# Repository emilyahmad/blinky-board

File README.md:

# Blinky board

This toro inoue inspired 555 LED chaser board contains 2 IC's: CD4017 to control LED's flashing and get input from NE555P, 2 header pins to power the circuit, standard capacitors and resistors, and of course LEDs. LEDs blink using the 555's astable mode to produces a continuous oscillating signal by toggling its output between high and low Made with help from @Tanishq Goyal qnd @CAN's guides on stasis.

# Photos

| Schematic                          | PCB                    | 3D Viewer            |
| ---------------------------------- | ---------------------- | -------------------- |
|  |  |  |

# Physical PCB / After Soldering

| Front                              | Back                             | Powered                                 |
| ---------------------------------- | -------------------------------- | --------------------------------------- |
|  |  |  |

# BOM

(Technically just using the blinky board kit from Hack Club)

| Item                                    | Purpose                          | Quantity |
| --------------------------------------- | -------------------------------- | -------- |
| C1                                      | 1F capacitor                     | 1        |
| C2                                      | .1F capacitor                    | 1        |
| D1, D2, D3, D4, D5, D6, D7, D8, D9, D10 | LEDs various colors              | 10       |
| J1                                      | 01x02 pin socket                 | 1        |
| J2                                      | 01x01 pin socket                 | 1        |
| R1                                      | 1k resistor                      | 1        |
| RV1                                     | 470 ohm resistor                 | 1        |
| U1                                      | NE555P IC (with timer we'll use) | 1        |
| U2                                      | 4017 IC (extend GPIO of NE555P)  | 1        |

Total: $10.60

```
⠀⠀⠀⠀⠀⠀⠀⠀⠀⠀⠀⠀⠀⠀⠀⠀⠀⠀⠀⠀⠀⠀⠀⠀⠀⠀⠀⠀⠀⠀⠀⠀⣠⠀⠀⠀⠀⠀⠀⠀⠀⠀⠀⠀⠀⠀⠀⠀⠀⠀⠀⠀⠀⠀⠀⠀
⠀⠀⠀⠀⠀⠀⠀⠀⠀⠀⠀⠀⠀⠀⠀⢀⠀⠀⠀⠀⠀⠀⠀⠀⠀⠀⠀⠀⠀⠀⠀⡜⠀⠑⡀⠀⠀⠀⠀⠀⠀⠀⠀⠀⠀⠀⠀⠀⠀⠀⠀⠀⠀⠀⠀⠀
⠀⠀⠀⠀⠀⠀⠀⠀⠀⠀⠀⠀⠀⠀⢀⠇⠑⢄⠀⠀⠀⠀⠀⠀⠀⠀⠀⠀⠀⢀⡾⠀⠀⠀⠈⢂⠀⠀⠀⠀⠀⠀⠀⠀⠀⠀⠀⠀⠀⠀⠀⠀⠀⠀⠀⠀
⠀⠀⠀⠀⠀⠀⠀⠀⠀⠀⠀⠀⠀⠀⡌⠀⠀⠀⠑⢆⡀⠀⠀⠀⠀⠀⠀⠀⠀⠺⠄⣀⠀⠀⠀⠀⠑⡀⠀⠀⠀⠀⠀⠀⠀⠀⠀⠀⠀⠀⠀⠀⠀⠀⠀⠀
⠀⠀⠀⠀⠀⠀⠀⠀⠀⠀⠀⠀⠀⡘⠀⠀⠀⠀⣀⠜⠃⠀⠀⠀⠀⠀⠀⠀⠀⠀⠀⠀⠈⠑⠀⠤⣀⠈⢆⠀⠀⠀⠀⠀⠀⠀⢀⡸⠄⠀⠀⠀⠀⠀⠀⠀
⠀⠀⠀⠀⠀⠀⠀⠀⠀⠀⠀⠀⢠⠃⠀⢀⠤⠊⠀⠀⠀⠀⠀⠀⠀⠀⠀⠀⠀⠀⠀⠀⠀⠀⠀⠀⠀⠁⠀⠑⠄⠀⠀⠀⠀⣀⡞⠁⠀⠀⢀⡀⠀⠀⠀⠀
⠀⠀⠀⠀⣤⠄⠀⠀⠀⠀⠀⢀⠋⡠⠔⠁⠀⠀⠀⠀⠀⠀⠀⠀⠀⠀⠀⠀⠀⠀⠀⠀⠀⣀⣤⠶⠒⠛⠉⠉⠈⢂⠀⠀⠀⠛⠀⣀⣤⠾⠛⠁⠀⠀⠀⠀
⠀⠀⠀⠀⠈⠳⣤⡀⠀⠀⠀⡎⠉⣀⣀⣀⣠⣄⣀⣀⠀⠀⠀⠀⠀⠀⠀⠀⠀⠀⠀⣶⣿⣿⠶⠶⠶⠶⠶⠶⢤⣀⠱⠀⠀⠀⠀⠉⠈⠀⠀⠀⠀⠀⠀⠀
⠀⠺⢦⣄⡠⠀⠉⠁⠀⠀⠸⠐⠋⠁⠀⢀⣀⣤⣽⣿⠿⠃⠀⠀⠀⠀⠀⠀⠀⠀⠀⠀⠈⠉⠛⠷⣦⣄⡀⠀⠀⠁⠀⠱⡀⠀⠀⠐⠓⠚⠛⠛⠀⠀⠀⠀
⠀⠀⠀⠀⠉⠛⠀⠀⠀⢀⠇⣠⠴⠶⠛⠉⣡⡾⠟⠁⠀⠀⠀⠀⠀⠀⠀⠀⠀⠀⠀⠀⠀⠀⠀⢀⠀⠈⠙⠷⢦⡀⠀⠀⢠⠀⠀⠀⠀⠀⠀⠀⠀⠀⠀⠀
⠠⡤⠤⠤⠼⠀⠀⠀⠀⢸⠀⠀⠀⢀⣤⡾⠋⠀⠀⠀⠀⠀⣀⣀⣤⣤⣶⡶⠶⠶⠿⢿⣷⠀⡐⠁⠀⠀⠀⠀⠀⠈⠒⠤⡀⠆⠀⠀⠀⠀⠀⠀⠀⠀⠀⠀
⠀⠀⠀⠀⠀⠀⠀⠀⠀⡇⠀⢀⣴⠿⠩⠤⠄⣀⠀⠀⠀⣿⡟⠋⠉⠀⠀⠀⠀⠀⠀⠀⣿⠀⢇⠀⠀⠀⠀⠀⠀⠀⠀⠀⠈⢾⠀⠀⠀⠀⠀⠀⠀⠀⠀⠀
⠀⠀⠀⠀⠀⠀⠀⠀⠀⠄⠀⡸⠁⠀⠀⠀⠀⠀⠙⢄⠀⢻⣇⠀⠀⠀⠀⠀⠀⠀⠀⠀⣿⠀⠈⠢⠄⣀⠀⠀⠀⠀⠀⢀⡠⠜⢣⠀⠀⠀⠀⠀⠀⠀⠀⠀
⠀⠀⠀⠀⠀⠀⠀⠀⠀⠂⠰⠁⠀⠀⠀⠀⠀⠀⠀⢸⠄⠘⣿⡄⠀⠀⠀⠀⠀⠀⠀⠀⣿⠀⠀⠀⠀⠀⠈⠁⠀⠈⠉⠁⠀⠀⠀⠆⠀⠀⠀⢀⠀⠀⠄⠀
⠀⠀⠀⠀⠀⠀⠀⠀⠀⠁⢇⠀⠀⠀⠀⠀⢀⡠⠔⠁⠀⠀⠹⣿⣄⠀⠀⠀⠀⠀⠀⢰⡿⠀⠀⠀⠀⠀⠀⠀⠀⠀⠀⠀⠀⠀⠀⡰⠀⡠⠐⠁⠀⠀⠀⡆
⠀⠀⠀⠀⠀⠀⠀⠀⠀⠀⠈⠓⠂⠒⠊⠉⠀⠀⠀⠀⠀⠀⠀⠘⢿⣧⣄⠀⠀⠀⢀⣾⠃⠀⠀⠀⠀⠀⠀⠀⠀⠀⠀⠀⠀⠀⣠⠇⠊⠀⠀⠀⢀⠄⠊⠀
⠀⠀⠀⠀⠀⠀⠀⠀⠀⡄⠀⠀⠀⠀⠀⠀⠀⠀⠀⠀⠀⠀⠀⠀⠀⠈⠛⠷⣦⣤⡾⠃⠀⠀⠀⠀⠀⠀⠀⠀⠀⠀⠀⢀⡴⠚⠁⠀⠀⠀⡠⠂⠁⠀⠀⠀
⠀⠀⠀⠂⠤⠀⣀⠀⠀⢳⡀⠀⠀⠀⠀⠀⠀⠀⠀⠀⠀⠀⠀⠀⠀⠀⠀⠀⠈⠈⠀⠀⠀⠀⠀⠀⠀⠀⠀⠀⣀⠴⠊⠁⠀⠀⠀⡠⠔⠁⠀⠀⠀⠀⠀⠀
⡀⠀⠀⠀⠀⠀⠀⠈⠑⠂⠙⠢⠤⣀⡀⠀⠀⠀⠀⠀⠀⠀⠀⠀⠀⠀⠀⠀⠀⠀⠀⠀⠀⠀⠀⠇⢀⡠⠔⠋⠀⠀⠀⠀⡠⠐⠉⠀⠀⠀⠀⠀⠀⠀⠀⠀
⠈⠀⠐⠂⠤⢀⡀⠀⠀⠀⠀⠀⠀⠀⠉⠉⠀⠐⠒⠂⠀⠤⢤⠀⠀⠀⠀⠀⠀⠀⠀⠀⠀⠀⠀⠞⠁⠀⠀⠀⣀⠄⠂⠁⠀⠀⠀⠀⠀⠀⠀⠀⠀⠀⠀⠀
⠀⠀⠀⠀⠀⠀⠀⠀⠉⠀⠒⠀⠀⠀⠀⠀⠀⠀⠀⠀⠀⠀⠀⠀⠀⠀⠀⠀⠀⠀⠀⠀⠀⠀⠀⠀⣀⠠⠒⠁⠀⠀⠀⠀⠀⠀⠀⠀⠀⠀⠀⠀⠀⠀⠀⠀
⠀⠀⠀⠀⠀⠀⠀⠀⠀⠀⠀⠀⠀⠀⠀⠀⠀⠀⠀⠀⠀⠀⠀⠀⠀⠀⠀⠀⠀⠀⠀⠀⠀⠀⠀⢨⠀⠀⠀⠀⠀⠀⠀⠀⠀⠀⠀⠀⠀⠀⠀⠀⠀⠀⠀⠀
⠀⠀⠀⠀⠀⠀⠀⠀⠀⠀⠀⠀⠀⠀⠀⠀⠀⠀⠀⠀⠀⠀⠀⠀⠀⠀⠀⠀⠀⠀⠀⠀⠀⠀⠀⠐⠀⠀⠀⠀⠀⠀⠀⠀⠀⠀⠀⠀⠀⠀⠀⠀⠀⠀⠀⠀
```

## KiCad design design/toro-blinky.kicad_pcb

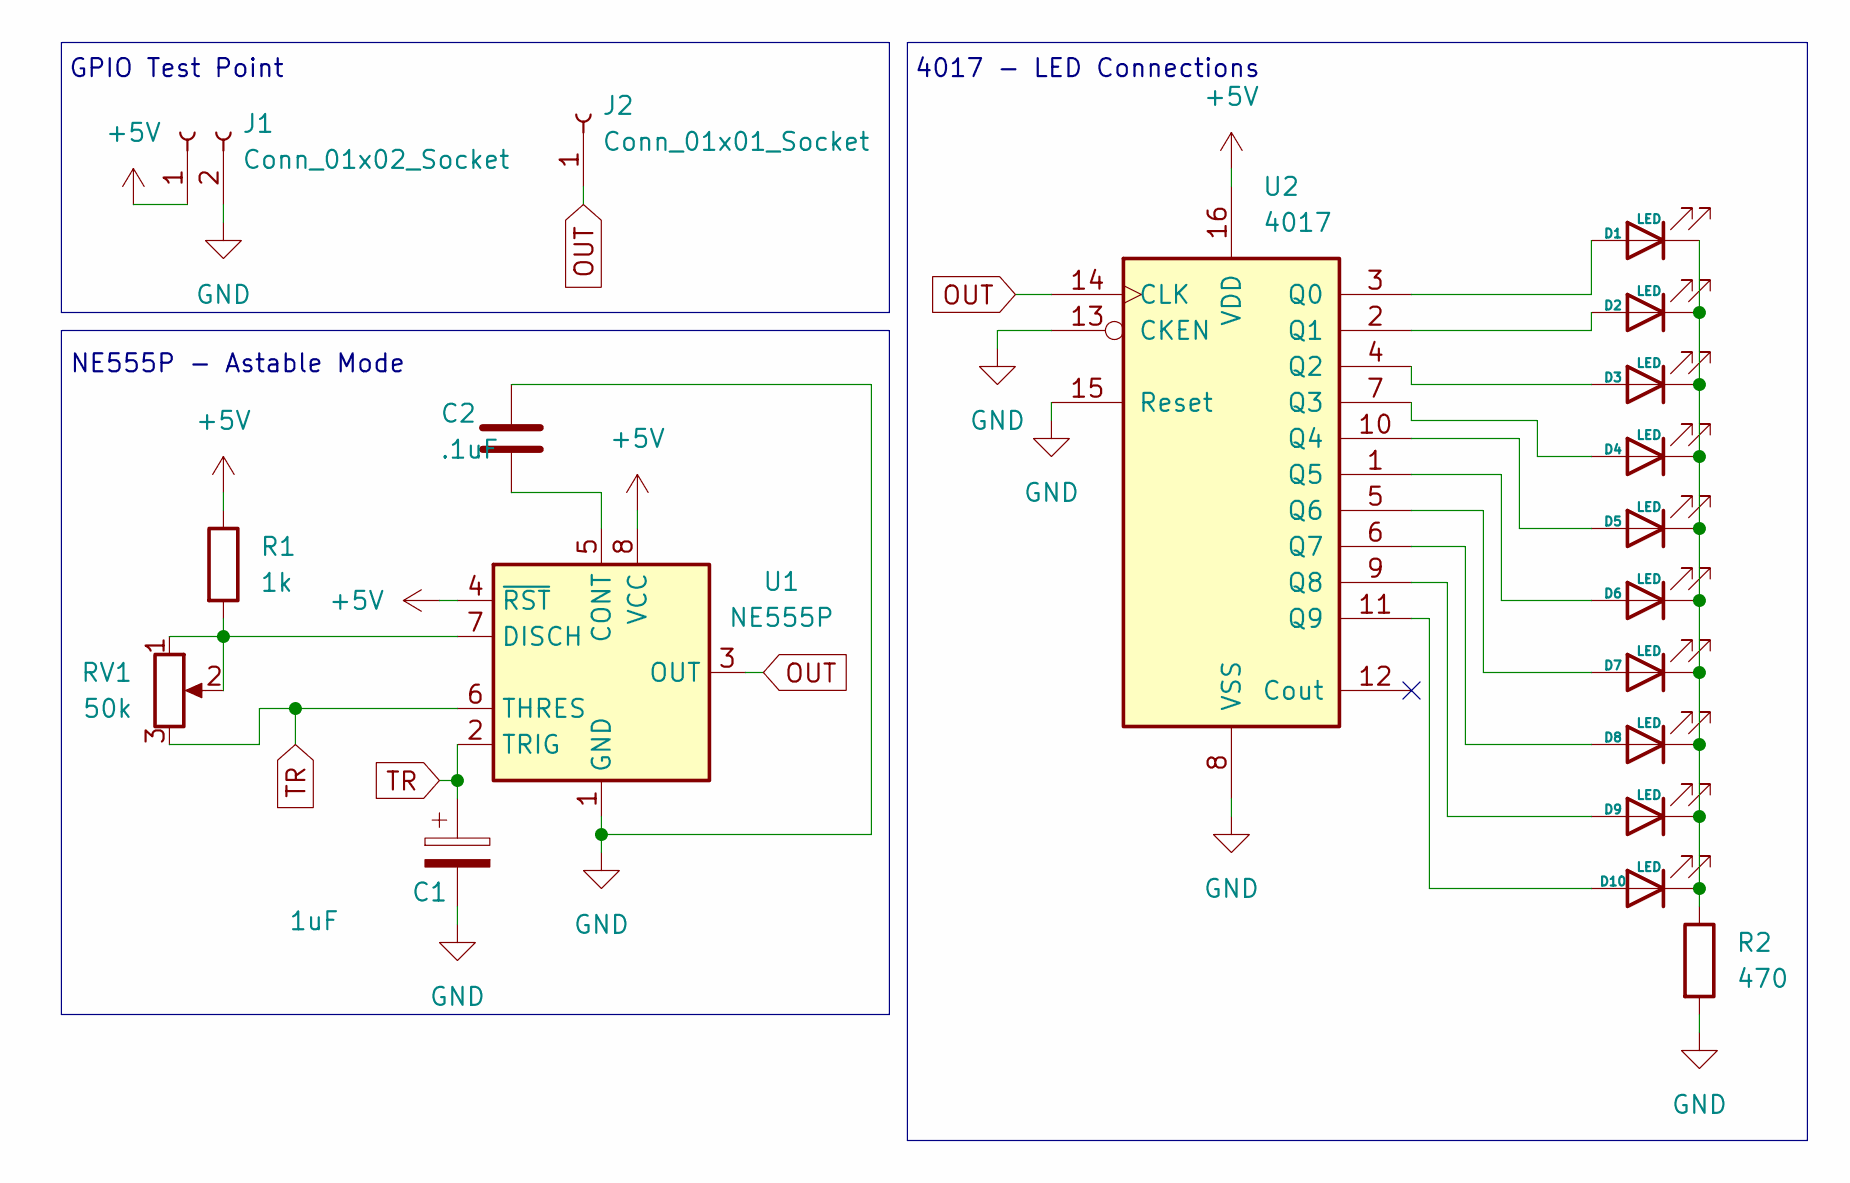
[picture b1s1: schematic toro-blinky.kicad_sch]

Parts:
C1: 1uF; CP_Radial_D5.0mm_P2.00mm
C2: .1uF; CP_Radial_D5.0mm_P2.00mm
D1, D2, D3, D4, D5, D6, D7, D8, D9, D10: LED; LED_D3.0mm
J1: Conn_01x02_Socket; PinHeader_1x02_P2.54mm_Vertical
J2: Conn_01x01_Socket; PinHeader_1x02_P2.54mm_Vertical
R1: 1k; R_Axial_DIN0207_L6.3mm_D2.5mm_P7.62mm_Horizontal
R2: 470; R_Axial_DIN0207_L6.3mm_D2.5mm_P7.62mm_Horizontal
RV1: 50k; Potentiometer_Vishay_T93YA_Vertical
U1: NE555P; DIP-8_W7.62mm
U2: 4017; N16

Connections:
+5V: J1.1, R1.1, U1.4 (~RST), U1.8 (VCC), U2.16 (VDD)
GND: C1.2, C2.1, J1.2, R2.2, U1.1 (GND), U2.8 (VSS), U2.13 (CKEN), U2.15 (Reset)
unnamed: D1.2 (A), U2.3 (Q0)
unnamed: D1.1 (K), D2.1 (K), D3.1 (K), D4.1 (K), D5.1 (K), D6.1 (K), D7.1 (K), D8.1 (K), D9.1 (K), D10.1 (K), R2.1
unnamed: D2.2 (A), U2.2 (Q1)
unnamed: D3.2 (A), U2.4 (Q2)
unnamed: D4.2 (A), U2.7 (Q3)
unnamed: D5.2 (A), U2.10 (Q4)
unnamed: D6.2 (A), U2.1 (Q5)
unnamed: D7.2 (A), U2.5 (Q6)
unnamed: D8.2 (A), U2.6 (Q7)
unnamed: D9.2 (A), U2.9 (Q8)
unnamed: D10.2 (A), U2.11 (Q9)
unnamed: C2.2, U1.5 (CONT)
unnamed: R1.2, RV1.1, RV1.2, U1.7 (DISCH)
OUT: J2.1 (Pin_1_1), U1.3 (OUT), U2.14 (CLK)
TR: C1.1, RV1.3, U1.2 (TRIG), U1.6 (THRES)

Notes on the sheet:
GPIO Test Point
NE555P - Astable Mode
4017 - LED Connections

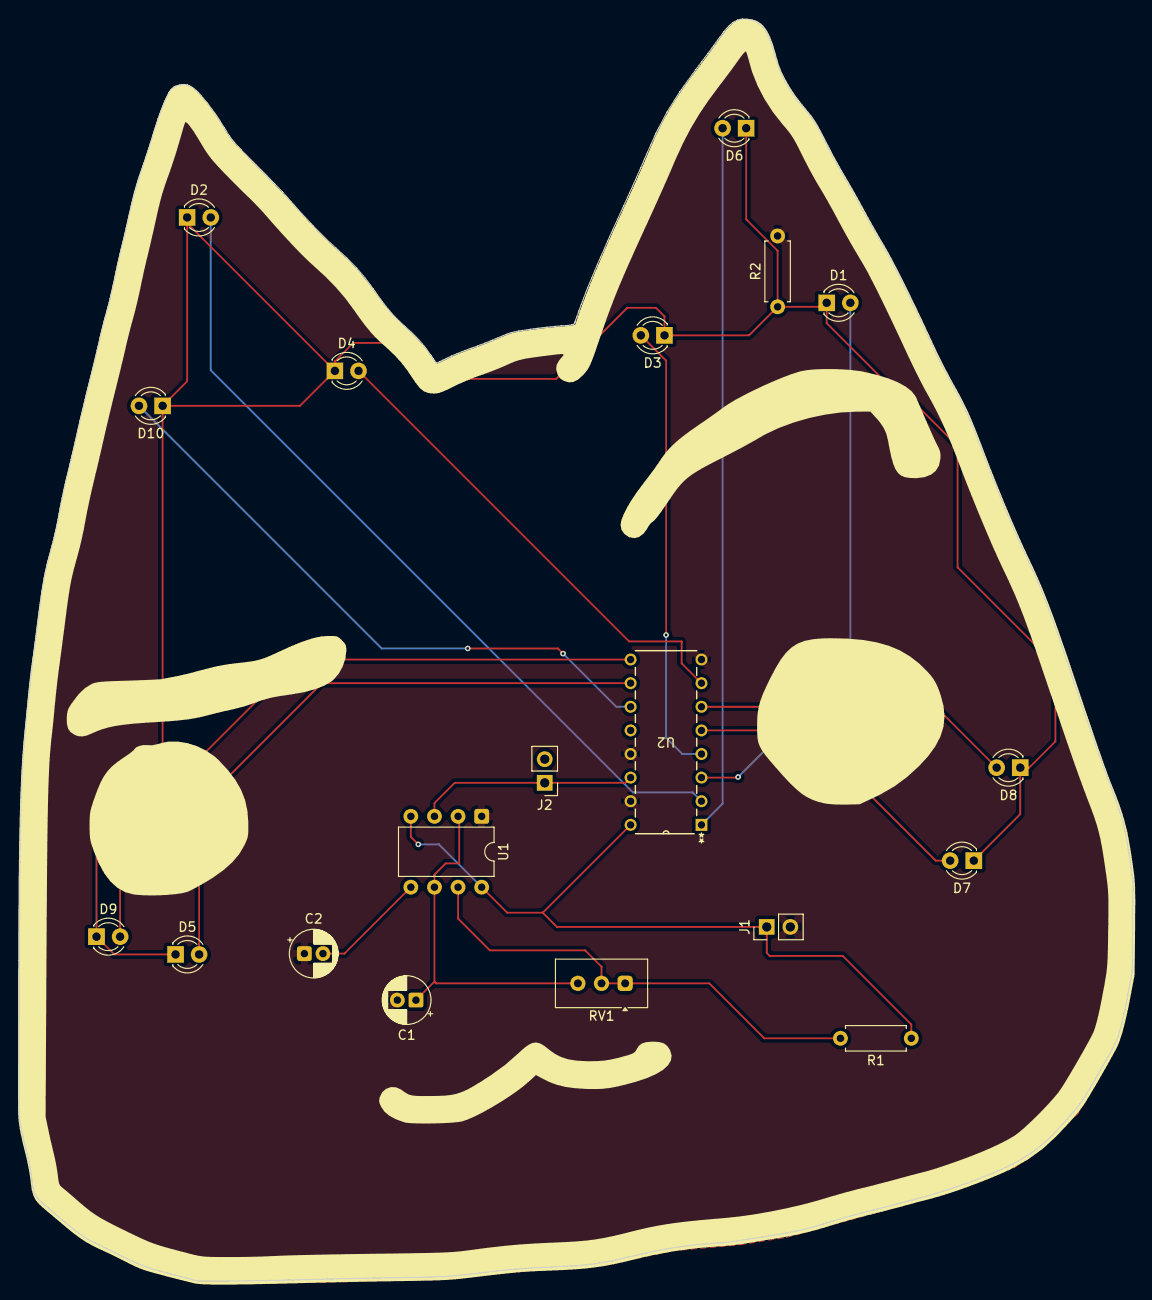
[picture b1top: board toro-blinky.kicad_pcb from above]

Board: 2 copper layers, 119.8 x 135.7 mm, 19 parts (0 on the bottom side), 17 nets.

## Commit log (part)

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2026-04-04 we brainstorming
2026-05-04 cute ascii
2026-05-04 added bom (commented)
2026-05-04 organizing
2026-05-04 update readme, add imgs
2026-05-04 readme update
2026-05-05 update BOM
2026-06-26 Dryfitting components
